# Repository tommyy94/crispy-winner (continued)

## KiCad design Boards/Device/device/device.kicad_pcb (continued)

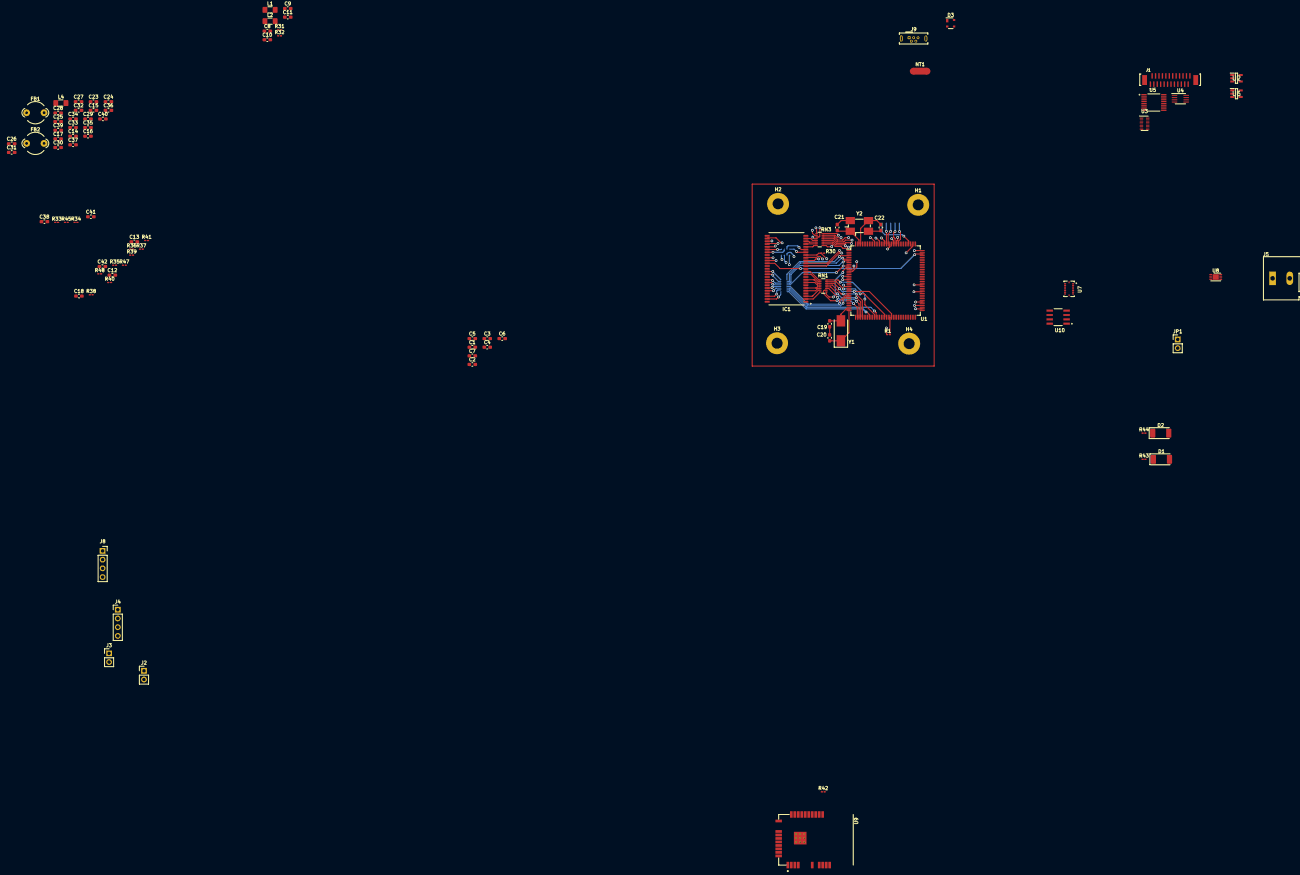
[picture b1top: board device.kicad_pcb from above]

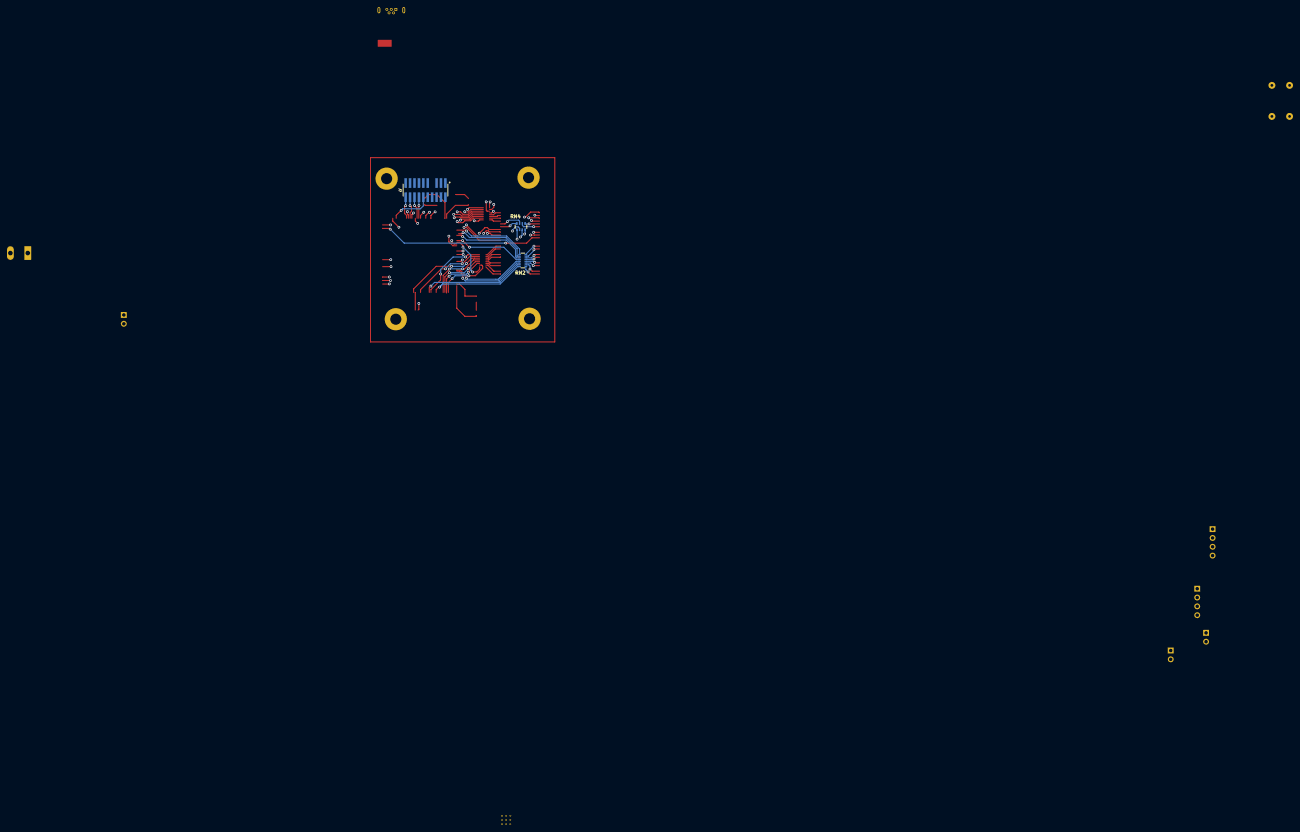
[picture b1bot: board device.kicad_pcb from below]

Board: 4 copper layers, 100 parts (3 on the bottom side), 153 nets.

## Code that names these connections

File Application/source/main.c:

#include "same70.h"
#include <string.h>
#include "socket/include/socket.h"

/* Application includes */
#include "system.h"
#include "err.h"
#include "throttle.h"
#include "gyro.h"
#include "wireless.h"
#include "distance.h"

/* RTOS includes */
#include "RTOS.h"
#include "BSP.h"

/* Driver includes */
#include "twi.h"

#define MESSAGE_ALIGNMENT                       (4u)

/* High number = high priority */
#define TASK_STARTUP_PRIORITY                   (70u)
#define TASK_WIRELESS_PRIORITY                  (69u)
#define TASK_SENSOR_PRIORITY                    (62u)
#define TASK_VIDEO_PRIORITY                     (63u)
#define TASK_CONTROL_PRIORITY                   (61u)
#define TASK_ERROR_PRIORITY                     (57u)
#define TASK_RTC_PRIORITY                       (58u)
#define TASK_THROTTLE_PRIORITY                  (59u)
#define TASK_GYRO_PRIORITY                      (56u)
#define TASK_DISTANCE_PRIORITY                  (60u)
#define TASK_IMAGE_PRIORITY                     (68u)


static OS_STACKPTR int stackErr[128]        __attribute__((aligned(8)));
       OS_TASK         errTCB;
static OS_STACKPTR int stackRtc[128]        __attribute__((aligned(8)));
       OS_TASK         rtcTCB;
static OS_STACKPTR int stackWireless[2048]  __attribute__((aligned(8)));
static OS_TASK         wirelessTCB;
static OS_STACKPTR int stackSensor[1024]     __attribute__((aligned(8)));
static OS_TASK         sensorTCB;
static OS_STACKPTR int stackControl[512]    __attribute__((aligned(8)));
static OS_TASK         controlTCB;
static OS_STACKPTR int stackVideo[1024]      __attribute__((aligned(8)));
static OS_TASK         videoTCB;
static OS_STACKPTR int stackThrottle[512]   __attribute__((aligned(8)));
static OS_TASK         throttleTCB;
static OS_STACKPTR int stackGyro[512]       __attribute__((aligned(8)));
static OS_TASK         gyroTCB;
static OS_STACKPTR int stackStartup[512]    __attribute__((aligned(8)));
static OS_TASK         startupTCB;
static OS_STACKPTR int stackDistance[256]   __attribute__((aligned(8)));
       OS_TASK         distanceTCB;
static OS_STACKPTR int stackImage[2048]     __attribute__((aligned(8)));
       OS_TASK         imageTCB;


OS_QUEUE          throttleQ;
OS_QUEUE          gyroQ;
OS_QUEUE          tsQ;
OS_EVENT          dmaEvt;
OS_EVENT          svEvt;
OS_EVENT          wlessEvt;
OS_MAILBOX        twiMbox;
OS_SEMAPHORE      twiSema;
OS_MUTEX          wlessMutex;
OS_MUTEX          twiMutex;
OS_MUTEX          traceMutex;
#ifdef EVABOARD_WORKAROUND
OS_MUTEX          evabrdWaMutex;
#endif /* EVABOARD_WORKAROUND */

#define Q_MSG_SIZE  (1u)
#define Q_MSG_CNT   (32u)
#define Q_SIZE      (Q_MSG_CNT * (Q_MSG_SIZE + OS_Q_SIZEOF_HEADER) + MESSAGE_ALIGNMENT)
char              _twiMemBuffer[sizeof(TWI_Msg *)];
char              _tsMemBuffer[Q_SIZE];
char              _gyroMemBuffer[Q_SIZE];
char              _throttleMemBuffer[Q_SIZE];


extern void Wireless_Task(void *arg);
extern void Sensor_Task(void *arg);
extern void Control_Task(void *arg);
extern void Video_Task(void *arg);
extern void err_Task(void *arg);
extern void RTC_Task(void *arg);
extern void throttle_Task(void *arg);
extern void gyro_Task(void *arg);
extern void Distance_Task(void *arg);
extern void Image_Task(void *arg);
static void Startup_Task(void *arg);

static void OS_InitTasks(void);
static void OS_InitServices(void);


/**
 * @brief   Initialize RTOS and start the scheduler.
 *
 * @param   None
 *
 * @retval  None
 */
int main(void)
{
    OS_Init();
    OS_InitHW();
    OS_InitTasks();
    OS_Start();
}


/**
 * @brief   Startup task.
 *
 * @param   None
 *
 * @retval  None
 */
static void OS_InitTasks(void)
{
    OS_TASK_CREATEEX(&startupTCB,   "Startup",  TASK_STARTUP_PRIORITY,  Startup_Task,   stackStartup,   NULL);
    OS_TASK_CREATEEX(&wirelessTCB,  "Wireless", TASK_WIRELESS_PRIORITY, Wireless_Task,  stackWireless,  NULL);
    OS_TASK_CREATEEX(&sensorTCB,    "Sensor",   TASK_SENSOR_PRIORITY,   Sensor_Task,    stackSensor,    NULL);
    //OS_TASK_CREATEEX(&controlTCB,   "Control",  TASK_CONTROL_PRIORITY,  Control_Task,   stackControl,   NULL);
    OS_TASK_CREATEEX(&videoTCB,     "Video",    TASK_VIDEO_PRIORITY,    Video_Task,     stackVideo,     NULL);
    OS_TASK_CREATEEX(&rtcTCB,       "RTC",      TASK_RTC_PRIORITY,      RTC_Task,       stackRtc,       NULL);
    OS_TASK_CREATEEX(&errTCB,       "Error",    TASK_ERROR_PRIORITY,    err_Task,       stackErr,       NULL);
    OS_TASK_CREATEEX(&gyroTCB,      "Gyro",     TASK_GYRO_PRIORITY,     gyro_Task,      stackGyro,      NULL);
    OS_TASK_CREATEEX(&throttleTCB,  "Throttle", TASK_THROTTLE_PRIORITY, throttle_Task,  stackThrottle,  NULL);
    OS_TASK_CREATEEX(&distanceTCB,  "Distance", TASK_DISTANCE_PRIORITY, Distance_Task,  stackDistance,  NULL);
    OS_TASK_CREATEEX(&imageTCB,     "Image",    TASK_IMAGE_PRIORITY,    Image_Task,     stackImage,     NULL);
}


/**
 * @brief   Create RTOS events, queues, mutexes, semaphores, etc.
 *
 * @param   None
 *
 * @retval  None
 */
static void OS_InitServices(void)
{
    /* Events */
    OS_EVENT_CreateEx(&dmaEvt, OS_EVENT_MASK_MODE_AND_LOGIC);
    OS_EVENT_CreateEx(&svEvt, OS_EVENT_MASK_MODE_OR_LOGIC);
    OS_EVENT_CreateEx(&wlessEvt, OS_EVENT_MASK_MODE_OR_LOGIC);

    /* Queues */
    OS_QUEUE_Create(&throttleQ, &_throttleMemBuffer, sizeof(_throttleMemBuffer));
    OS_QUEUE_Create(&gyroQ, &_gyroMemBuffer, sizeof(_gyroMemBuffer));
    OS_QUEUE_Create(&tsQ, &_tsMemBuffer, sizeof(_tsMemBuffer));

    /* Mailboxes */
    OS_MAILBOX_Create(&twiMbox, sizeof(TWI_Msg *), 1, &_twiMemBuffer);

    /* Semaphores */
    OS_SEMAPHORE_Create(&twiSema, 0);

    /* Mutexes */
    OS_MUTEX_Create(&wlessMutex);
    OS_MUTEX_Create(&twiMutex);
    OS_MUTEX_Create(&traceMutex);

    /* SPI0 and ISI share pins in SAME70 Xplained evaluation kit:
     * - PD20: SPI0_MISO only
     * - PD21: SPI0_MOSI / ISI_D1
     * - PD22: SPI0_SCK / ISI_D0
     * - PD25: SPI0_SS / ISI_VSYNC
     *
     * Therefore the pins have to be reconfigured
     * before operating with SPI0/ISI peripheral.
     */
#ifdef EVABOARD_WORKAROUND
    OS_MUTEX_Create(&evabrdWaMutex);
#endif /* EVABOARD_WORKAROUND */
}


static void Startup_Task(void *arg)
{
    (void)arg;
    OS_InitServices();

    BSP_Init();

    OS_TASK_Terminate(NULL);
}

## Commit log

2022-04-07 Add WINC3400 drivers
2022-04-07 Move RTT to it's own sections
    Clear .RTT_Buffer on startup
    Enable MPU
2022-04-07 Add PMC driver
2022-04-07 Rename PORT to IO
2022-04-07 Update memory map
2022-04-07 Update gyro task stack size
2022-04-07 TWI gets stuck in loop when register view open in debugger
2022-04-07 MPU-6050 naming convention fix
2022-04-07 Add wireless application layer (WINC3400)
2022-04-07 Update Ozone debug file
2022-04-07 Remove fatfs get_fattime()
2022-04-07 Rename PORT to IO
    Add EXT IRQ handlers
2022-04-07 Add PMC driver
    Add MPU
2022-04-07 Fix SPI_DMA
2022-04-07 Fix DMA driver
    Still issue with burst size, now set to 1 as a workaround
2022-04-07 Use SEGGER provided CMSIS files
2022-04-07 Perform some minor changes to the project file
2022-04-15 Fix WINC1500 IRQ line
    - Pullup now enabled correctly
    - Interrupt now enabled ccorrectly
    - PIOD Interrupt handler named correctly
2022-04-15 Change TWI to polling method instead of interrupt based
2022-04-15 Split MPU-6050 Driver to separate files
2022-04-15 Add *.swp to .gitignore
2022-04-15 Improve logging
    Assert now reports function name instead of long file path
    Errors now reported with string instead of bit mask
2022-04-15 Temporarily suspend throttle task error reporting
2022-04-15 Read gyroscope every 10ms
    Disable gyro task error reporting
2022-04-18 Fix duplicate IRQ's from IO lines
2022-04-18 Use macros to test PIO instance validity
    Cosmetic change
2022-05-01 Add Sensor_Task()
2022-05-01 Refactor wireless.c
2022-05-01 Add dynamic socket signaling
2022-05-24 Move from TCP server to UDP server implementation
2022-05-25 Add Control_Task()
2022-05-25 UDP send and recv working
2022-05-25 Send dummy sensor data with transfer speed of 20Kbps
2022-10-26 Update project, fix crashes
2022-10-30 Add Video_Task() Sockets work
2022-10-31 Add Wi-Fi configuration to .gitignore
2022-10-31 Add Wi-Fi configuration template
2022-10-31 Add customized wifi_conf.h to the project
2022-10-31 Remove unused define MAIN_WIFI_M2M_PACKET_COUNT
2022-10-31 Include wifi_conf.h in wireless.c
2022-10-31 Add temporary jpg file to the project (tux.jpg)
2022-10-31 Add Wireless_Transmit() and Wireless_TransmitUnit() to transmit via UDP
2022-10-31 Add test value WLESS_EVT_INVALID to wireless events
2022-10-31 Eliminate magic number from buffer declaration
2022-10-31 Refactor functions declarations
2022-10-31 Document and refactor code
2022-11-04 Remove extra line endings and carriage returns
2022-11-04 Alternate between JPG's
2022-11-04 Add radio_frame.h
2022-11-04 Add missing jpgInv.c to the project file
2022-11-04 Add radio_frame handling
2022-11-05 Increase stackVideo and stackSensor to fit RadioFrame_t
2022-11-05 Add 2 bytes of padding to RadioFrame_t
2022-11-05 Serialize the RadioFrame_t struct
2022-11-05 Reduce trace pins from 2 to 1
2022-11-05 Remove inverted colors JPG test image
2022-11-05 Fix seqId assert
2022-11-05 Set Video_Task() interval to 100ms
2022-11-05 Remove sequenceId handling from task level
2022-11-05 Rename radioframe module to radiopacket
2022-11-08 Add distance measurement task
2022-11-08 Add ultrasonic distance sensor SRF05 driver
2022-11-08 Add external IRQ source detection to IO driver
2022-11-19 Ensure Edge Select is selected when both-edge detection event is used
2022-11-19 Add TC_ERROR
2022-11-21 Reorder IRQ priorities
    PIOD IRQ set as highest prio
2022-11-21 Use task events instead of mailbox in SRF05 module
2022-11-21 Add missing include
2022-11-21 Initialize TC0 Channel 0 in BSP_Init()
2022-11-21 FIx PIO IRQ edge/level detection
2022-11-21 Remove mask testing in PIO IRQ (already OR'ed by hardware)
2022-11-21 Remove redundant case from switch-case and remove useless register write
2022-11-21 Fix bug where piodFirstIrqN was not tracked correctly
2022-11-21 Adjust distance meas period to 100ms
2022-11-21 Add TC driver module
2022-11-21 Add wrappers for starting and stopping TC0 channel 0 counter
2022-11-21 Use separate handlers for SRF05 pulse end and trigger reception
2022-11-21 Fix a bug where use of mask and pin were mixed
2022-11-21 Read TC0 channel 0 counter at task level instead of at IRQ level
2022-11-21 Fix missing includes
2022-11-21 Reassign SRF05 pins so they won't clash with WINC3400 pins
2022-11-21 Fix typo
2022-11-24 Add Fixed Point Arithmetic header
    Includes macros for fixed pointer arithmetic
2022-11-24 Optimize US_TO_TICKS() macro
2022-11-24 Fix bug where TC_Delay() instantly finishes
    Fix TC issue where the counter value is sometimes read differently from zero just after a trigger, especially when a low frequency signal is selected as the clock.
    Increase clock frequency by setting clock divider to 8 instead of 128 fixing this issue.
    f_slck set to 18.75MHz
2022-11-25 All timers are 16-bits, but registers are 32-bit. Ensure we read 16 bits
2022-11-25 Add Doxygen comments
2022-11-25 Add Doxyfile
2022-11-25 Add Doxygen output folder to .gitignore
2022-11-25 Add mathjax to Doxygen
    Left align formulas
2022-11-25 Display formulas with mathjax
2022-11-25 Update SRF05 formula
2022-11-25 Add missing space
2022-11-26 Enable float support in printf
2022-11-26 Add EXTRACT_ALL
2022-11-26 Move TC tick/us macros to header
    Add TC0_CH0_TICKS_TO_US()
2022-11-26 Handle ticks instead of microseconds in TC driver
2022-11-26 Fix SRF05 formula
    Use floats instead of fixed point math
2022-11-26 TC driver handles ticks
2022-11-26 Fix bug where task event was not specified when waiting for an event
2022-11-26 Set SRF05 measurement period limit
    Distance measured according to this
2022-11-26 Print distance
2022-11-26 Refactor Journal module to err module
2022-11-26 Rename logWriter.* to err.*
2022-11-26 Enable RTC
2022-11-26 Increase Distance_Task size
2022-11-26 Refactor rtc_driver module variable and function names
2022-11-26 Remove confusing FreeRTOS naming convention prefixes
2022-11-26 Journal_vWriteError() was renamed to err_report()
2022-11-26 Add _t postfix to throttleChannel
2022-11-26 Enable Doxygen
2022-11-26 Journal_vWriteError() renamed to err_report()
2022-11-26 Reduce stackErr and stackRtc sizes to 512 bytes
2022-11-26 Enable throttle_Task
2022-11-27 Fix MPU-6050 self test bug
2022-11-27 Revert TWI back to interrupt based method
2022-11-27 Enable TWI0
2022-12-04 Enable PIOA, PIOB and PIOD in IO_Init()
2022-12-04 Add 1.3us bus free time between every TWI transfers
2022-12-04 Rename TC0_Ch0_Init() to TC0_Init()
2022-12-04 Fix TC_Delay() parameter name, we are passing ticks instead of us
2022-12-04 Fix TC0_Init() comment
2022-12-04 Enable TC0 channel 1 peripheral clock
2022-12-04 Fix critical tc_driver bug
    Wrong peripheral was accessed when accessing TCx greater than TC0
2022-12-04 #include "fpa.h" for FPA macros
2022-12-04 Fix pwm_driver channel map description
2022-12-04 Add Programmable Clock support to pmc_driver
2022-12-04 Rename PORT_IS_PIO() to IS_PIO()
2022-12-04 Print MPU-6050 chip ID
2022-12-04 Secure TWIHS0 with mutex
2022-12-04 Add TWI_TIMEOUT_MS macro
2022-12-04 Print hexadecimal letters as uppercase
2022-12-04 Fix bug where slave address was not set correctly in multi slave setup
2022-12-04 Add IS_TWIHS() macro
2022-12-04 Initialize TWI mutex at OS_InitServices()
2022-12-04 Add Image_Task
2022-12-04 Add preliminary OV5640 driver
2022-12-04 Enable gyro_Task but don't fill the queue
2022-12-11 Add delay functions for micro- and milliseconds
2022-12-11 Add OV5640_WriteReg() and OV5640_ReadReg()
2022-12-11 Add stm32-ov5640
2022-12-11 Modify stm32h747i_discovery_camera example for SAME70
2022-12-11 Add delay.c and delay.h files to the project
2022-12-11 Add C preprocessor define USE_CAMERA_SENSOR_OV5640=1
2022-12-11 Add include directories for the new OV5640 files
2022-12-12 TWIHS0 mutex now handled from upper level
2022-12-12 Add t_buff table to bus free time comment
2022-12-17 Load all OV5640 registers at once
    Previously mutex was lock and unlocked after each byte write
    Now mutex is locked at beginning of loading and unlocked afterwards
2022-12-18 Add C define EVABOARD_WORKAROUND
    Enables reconfiguring the shared IO pins before operating SPI0/ISI peripheral
    SPI0 and ISI share pins in SAME70 Xplained evaluation kit:
    - PD20: SPI0_MISO only
    - PD21: SPI0_MOSI / ISI_D1
    - PD22: SPI0_SCK / ISI_D0
    - PD25: SPI0_SS / ISI_VSYNC
2022-12-18 Map 16Mb external SDRAM
2022-12-18 Move test picture to external SDRAM
2022-12-18 Append external SDRAM to MPU
2022-12-18 Add SDRAMC driver prototype
2022-12-18 Fix missed rename and enable error reporting
2022-12-18 Configure MPU after SDRAM to avoid erratic(?) MemManage fault
2022-12-18 Add datasheet default value to exitSelfRefreshActiveDelay
2022-12-18 Refactor error reporting
2022-12-18 Move SRF05 to PIOC from PIOD
2022-12-18 Enable PIOC clock
2022-12-18 Add PIOC interrupt support
2022-12-18 Remove extra line breaks from SDRAMC_Init()
2022-12-18 Fix a bug where Image_Task attempts to unlock mutex it doesn't own
2022-12-18 Fix error_Task's name
2022-12-18 Refactor logging messages
2022-12-22 Default to no access
2022-12-22 Change WINC3400 IRQ and CE pins
2022-12-22 Add pinmux document
2022-12-26 Cosmetic changes
2022-12-26 Mark RAM as XN
2022-12-26 Fix a bug where section was initialized with non-initialized attributes
2022-12-26 Document used PCK
2022-12-26 Add sdram module
2022-12-26 Refactor sdramc_driver
2022-12-27 Configure IO pins
2022-12-27 Enable peripheral clock
2022-12-27 Enable ISI_IRQn
2022-12-27 Add ISI_Init()
2022-12-28 Initialize ISI in BSP_CAMERA_Init() instead of in BSP_Init()
2022-12-28 Fix pinmux
2023-01-02 Disable ETM
2023-01-02 This err_report() should not be here (wtf?)
2023-01-02 Fix WINC3400 IRQ pin
2023-01-05 Fix IO port width
2023-01-06 Increase SPI to 25 MHz
2023-01-06 Fix IRQ configuration sequence
    Install IRQ handler before enabling IRQ
    Enable pull-up before enabling IRQ
2023-01-06 Attach WINC3400 to EXT1 instead of using long jumper wires
2023-01-06 Enable IRQ and clear pending bit in NVIC only if it's disabled
2023-01-06 Fix IRQ configuration sequence removing a blank interrupt
2023-01-06 Add rest of the PIOx handlers
2023-01-06 Add log message informing successful configuration
2023-01-06 Use camera connector pins
2023-01-06 Send \r before \n to avoid extra line breaks in RTT viewer
2023-01-06 Remove unused error codes
2023-01-06 Fix a bug where evtMask was set to 0 resulting in missed error report
    Caused by casting OS_TASKEVENT_GetBlocked() result to Error_t which is uint8_t resulting in discarding bits greater than 0xFF
2023-01-06 Assert event count
2023-01-06 Handle a single event per task cycle
2023-01-06 Swap IO port and pins
2023-01-06 Disable camera code
2023-01-06 Remap PWM channels
    Now using only PWMC0
2023-01-06 Add isi_driver prototype
2023-01-06 Add ISI_Capture() call and do minor cleanup
2023-01-06 Update pinmux
2023-01-06 Add .~lock files to .gitignore
2023-01-06 Fix indent
2023-01-06 Use magic numbers instead of importing linker symbols
2023-01-07 Add trace module prototype
2023-01-09 Allocate pins for CAN1
2023-01-09 Remove PWM and use separate ESC's for each motor in the future
2023-02-05 Add schema+layout prototype
